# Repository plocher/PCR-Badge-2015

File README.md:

# PCR-Badge-2015
## License: CERN Open Hardware Licence v1.2

PCR-Badge-2015

## PCR Club Car Convention 2015
### ‘Duino Demo Board

* [Arduino source code](https://github.com/plocher/PCRdemo2015)

Once a year, the model railroaders in Northern California and Nevada (officially, the [Pacific Coast Region](http://www.pcrnmra.org)
of the [National Model Railroad Association](http://nmra.org)) host a convention.
2015's theme was [The Club Car](http://http://www.pcrnmra.org/conv2015/) - a nod towards the many vibrant railroad clubs in the area. 

Coincidentally, the convention overlapped the Bay Area Maker Faire's time slot, which made for some very long days indeed!

Because of the juxtaposition with the Faire, [railnerd](http://railnerd.blogspot.com/) and I decided to produce an <i>assemble it yourself</i>
"badge" for the railroad convention - after all, model train buffs
are all makers of one sort or another - and getting into animations
and layout control with a 'duino is a natural progression from
controlling trains with a packet network on the rails (via [Digital
Command Control](https://en.wikipedia.org/wiki/Digital_Command_Control))...

With judicious ebay and alibaba sleuthing, along with raiding some old stockpiles and a run to
a local surplus store, we managed to produce a 30-board run with a total per-board BOM cost of about $20!
(ICStation had 1602 LCDs for ~$3.10/ea, czb6721960@ebay had Pro Mini atmega328 5V 16M's for $2.50, etc...)

The PCR demo/badge board is a foundation for experimentation and learning about ‘duino programming and model railroad applications. 

It includes
  * An Arduino-compatible “DFR-pro-mini” clone module
  * A regulated 5v power supply
  * 9v battery (good for 6-8 hours runtime…) and adapter
  * 3x pushbuttons
  * 5x LEDs, arranged as a grade crossing and a signal head
  * A servo, and
  * A 2x16 LCD display
  * I2C connector for access to expanded IO devices

Brought to you by Railnerd and SPCoast, sources for DIY model railroad electronics ideas

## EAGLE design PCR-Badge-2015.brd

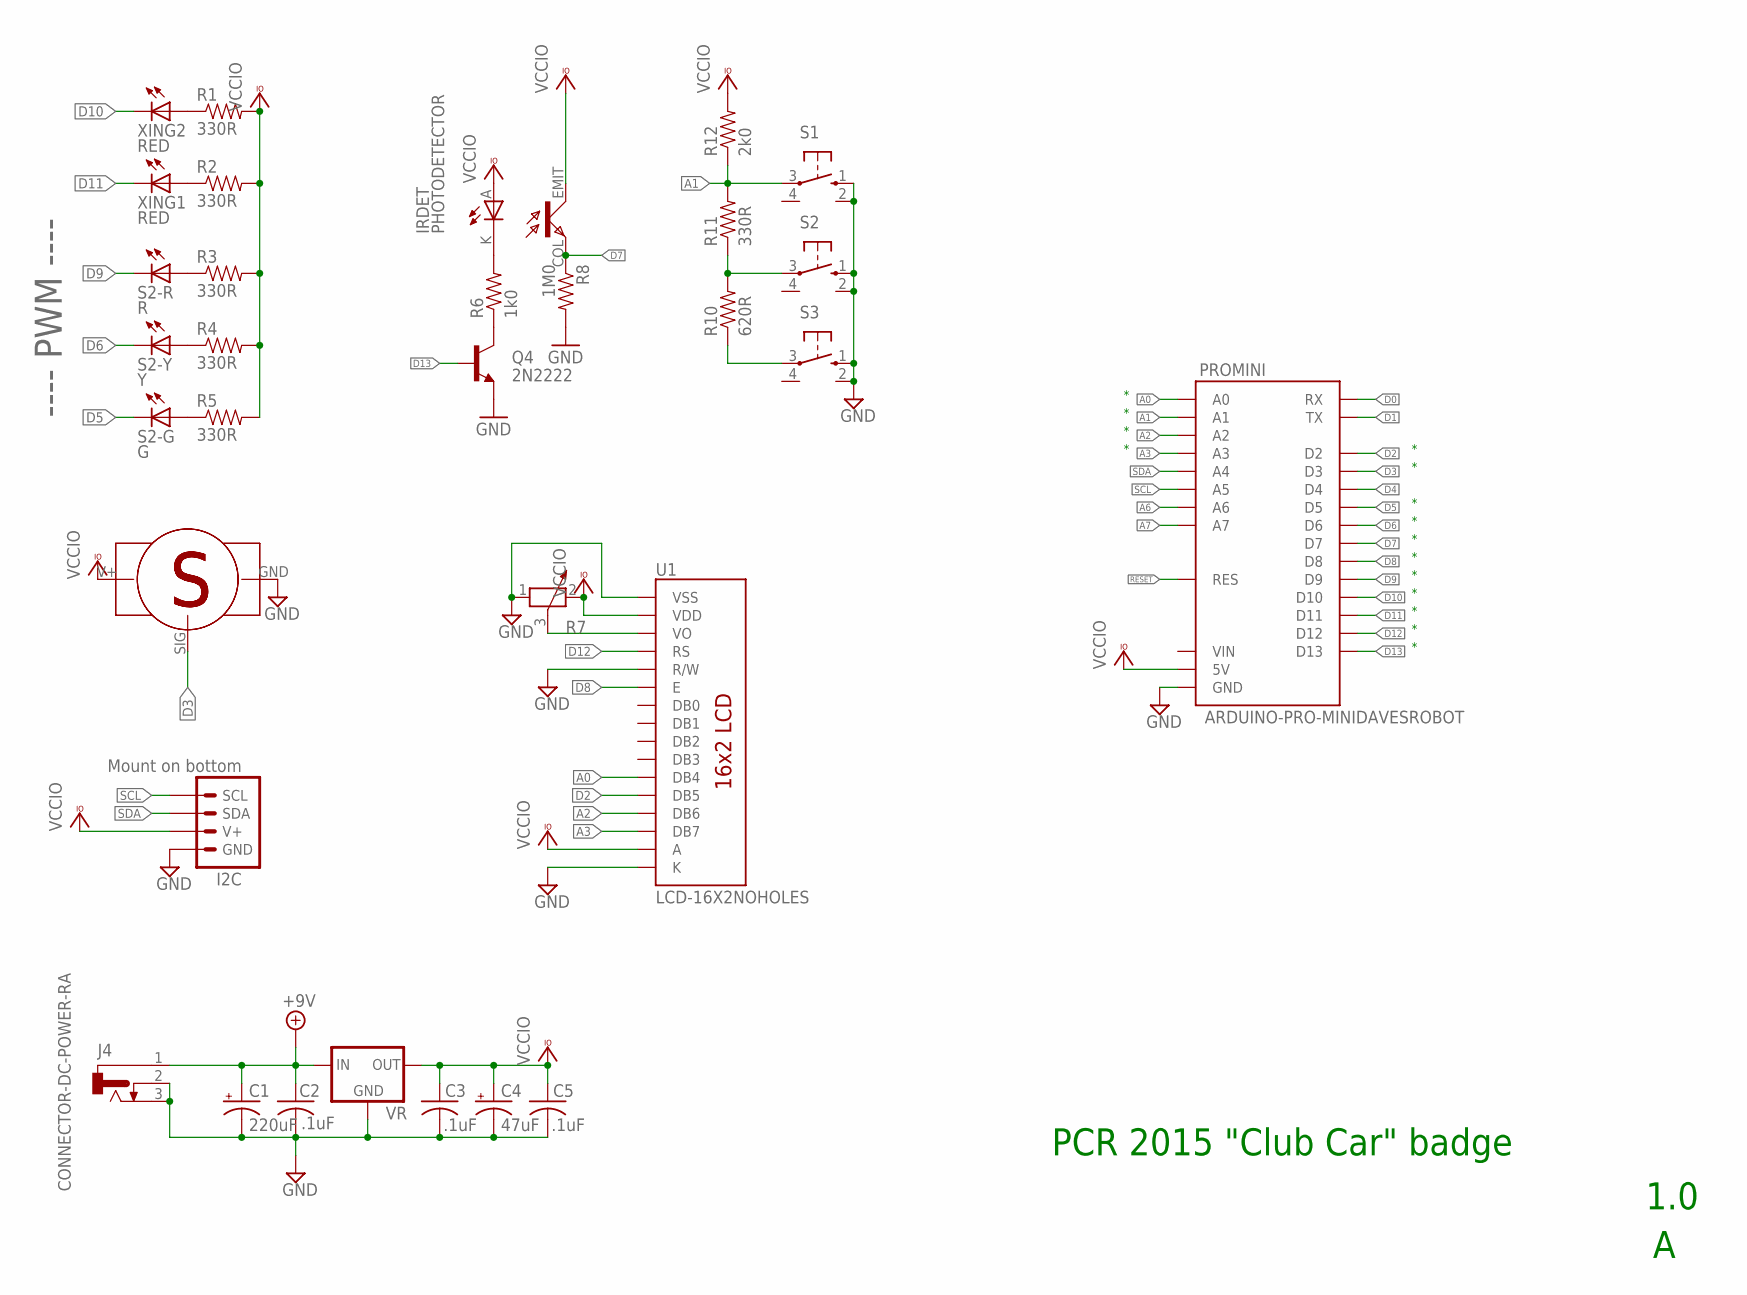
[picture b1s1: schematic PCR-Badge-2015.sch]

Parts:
C1: 220uF; E5-10.5
C2, C3, C5: .1uF; C050-024X044
C4: 47uF; E5-10.5
I2C: Mount on bottom; I2C
IRDET: PHOTODETECTOR; RPR220
J4: CONNECTOR-DC-POWER-RA; DCJ0202
POWER: 9-12vDC; POWER_USAGE
PROMINI: ARDUINO-PRO-MINIDAVESROBOT; ARDUINO_PRO_MINI_DAVEK
Q4: 2N2222; TO-92
R1, R2, R3, R4, R5, R11: 330R; 1/6W-RES
R6: 1k0; 1/6W-RES
R7: R-POTENTIOMETERB25U; B25U
R8: 1M0; 1/6W-RES
R10: 620R; 1/6W-RES
R12: 2k0; 1/6W-RES
S1, S2, S3: SWITCH-(ON)SMALLPADS; 4P-PTH-6.0X6.0X5.0H
S2-G: G; LED5MM
S2-R: R; LED5MM
S2-Y: Y; LED5MM
SERVO: SERVO
SERVO1: SERVO; SERVO-9G
U1: LCD-16X2NOHOLES; LCD-16X2_NOHOLES
VR: VREG_78XX-TO-220; TO-220-ALT
XING1, XING2: RED; LED5MM

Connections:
+9V: C1.+, C2.1, J4.1, VR.IN
A0: PROMINI.AD0 (A0), U1.11 (DB4)
A1: PROMINI.AD1 (A1), R11.2, R12.1, S1.3
A2: PROMINI.AD2 (A2), U1.13 (DB6)
A3: PROMINI.AD3 (A3), U1.14 (DB7)
A6: PROMINI.AD6 (A6)
A7: PROMINI.AD7 (A7)
D0: PROMINI.RX
D1: PROMINI.TX@1 (TX)
D2: PROMINI.D2, U1.12 (DB5)
D3: PROMINI.D3, SERVO.SIG (PWM)
D4: PROMINI.D4
D5: PROMINI.D5, S2-G.K (C)
D6: PROMINI.D6, S2-Y.K (C)
D7: IRDET.COL, PROMINI.D7, R8.1
D8: PROMINI.D8, U1.6 (E)
D9: PROMINI.D9, S2-R.K (C)
D10: PROMINI.D10, XING2.K (C)
D11: PROMINI.D11, XING1.K (C)
D12: PROMINI.D12, U1.4 (RS)
D13: PROMINI.D13, Q4.2 (B)
GND: C1.-, C2.2, C3.2, C4.-, C5.2, I2C.GND, J4.2, J4.3, PROMINI.GND@1 (GND), PROMINI.GND@2 (GND), PROMINI.GND@4 (GND), Q4.1 (E), R7.1, R8.2, S1.1 (S), S1.2 (S1), S2.1 (S), S2.2 (S1), S3.1 (S), S3.2 (S1), SERVO.GND, U1.1 (VSS), U1.5 (R/W), U1.16 (K), VR.GND
IRDRIVE4: Q4.3 (C), R6.1
unnamed: R1.1, XING2.A
unnamed: R2.1, XING1.A
unnamed: R3.1, S2-R.A
unnamed: R4.1, S2-Y.A
unnamed: R5.1, S2-G.A
unnamed: IRDET.K, R6.2
unnamed: R10.2, R11.1, S2.3
unnamed: R10.1, S3.3
RESET: PROMINI.RES, PROMINI.RES@1 (RES)
SCL: I2C.SCL, PROMINI.AD5 (A5)
SDA: I2C.SDA, PROMINI.AD4 (A4)
VCCIO: C3.1, C4.+, C5.1, I2C.V+, IRDET.A, IRDET.EMIT, PROMINI.5V, R1.2, R2.2, R3.2, R4.2, R5.2, R7.2, R12.2, SERVO.V+, U1.2 (VDD), U1.15 (A), VR.OUT
VO: R7.3, U1.3 (VO)

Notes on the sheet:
PCR 2015 "Club Car" badge
1.0
---- PWM ----

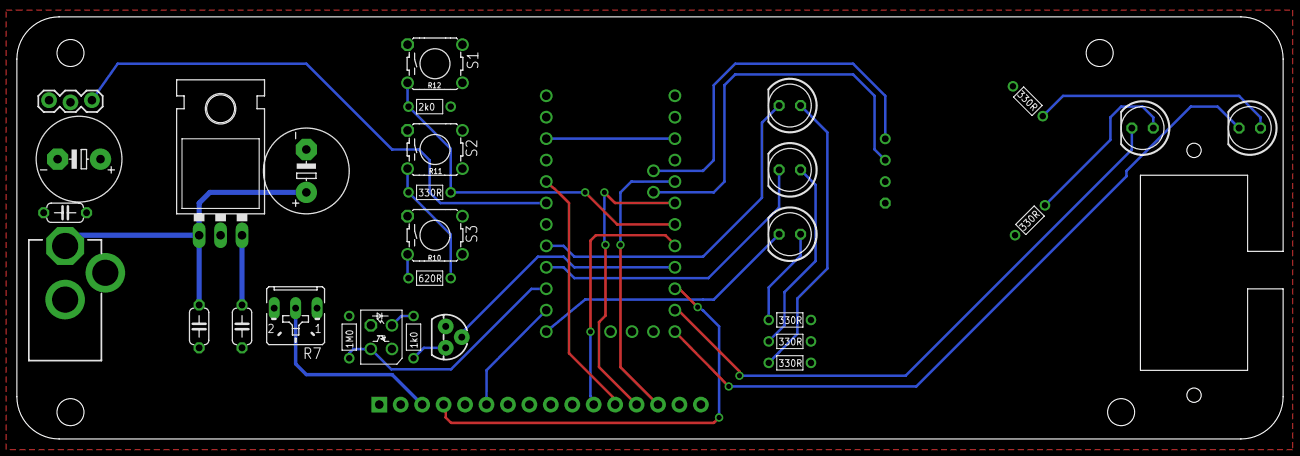
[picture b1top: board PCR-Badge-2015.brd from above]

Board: 2 copper layers, 150.0 x 50.0 mm, 34 parts (1 on the bottom side), 31 nets.

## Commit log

2019-12-03 add link to 'duino source code
2020-05-04 updated tags

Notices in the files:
parts and their libraries:
SparkFun-Displays: Licensing: CC v3.0 Share-Alike You are welcome to use this library for commercial purposes.
